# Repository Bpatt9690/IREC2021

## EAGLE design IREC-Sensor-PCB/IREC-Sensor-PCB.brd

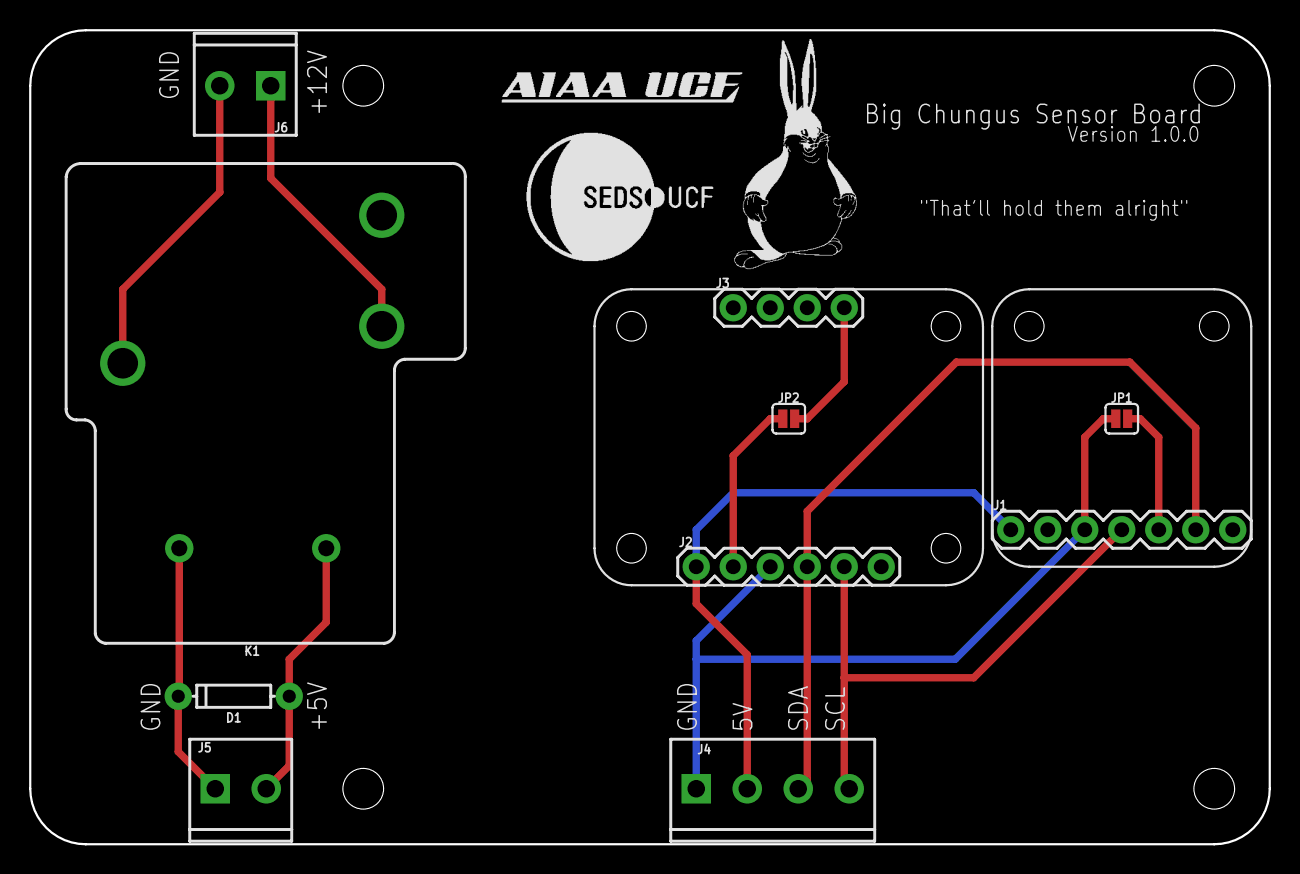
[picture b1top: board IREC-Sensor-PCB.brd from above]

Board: 2 copper layers, 85.1 x 55.9 mm, 11 parts (0 on the bottom side), 11 nets.

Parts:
D1: 200mA/100V/1V; DIODE-1N4148
FRAME1: FRAME-LETTER; CREATIVE_COMMONS
J1: 1X07
J2: 1X06
J3: 1X04
J4: SCREWTERMINAL-3.5MM-4
J5, J6: SCREWTERMINAL-3.5MM-2
JP1: HPT_ADDR; SMT-JUMPER_2_NO_SILK
JP2: AGM_ADDR; SMT-JUMPER_2_NO_SILK
K1: RELAY-SPDT-JQX-15F; RELAY-T90

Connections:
3V_AGM: J2.2, JP2.1
5V: J1.1, J2.1, J4.2
AD_AGM: J3.4, JP2.2
AD_HPT: J1.5, JP1.2
GND: J1.3, J2.3, J4.1, JP1.1
unnamed: D1.A, J5.2, K1.COIL2
unnamed: D1.C, J5.1, K1.COIL1
unnamed: J6.2, K1.MAIN
unnamed: J6.1, K1.NO
SCL: J1.4, J2.5, J4.4
SDA: J1.6, J2.4, J4.3

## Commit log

2020-08-04 Setting Up Repo
2020-08-04 Added backup for Launch_Pad_Files
2020-08-18 Fixed bug in cfTest.py
2020-08-27 Restructuring repo
2020-08-28 Added Sensor PCB files
2020-08-29 Updated Sensor PCB files
2020-08-30 Updated Logo Folder
2020-08-30 Set up board dimensions
2020-08-31 Completed layout
    Completed board layout
2020-08-31 Final 1.0.0 Board!
    Board is complete!
    - Adjusted board dimensions
    - Added relay
    - Added I2C address switches
2020-09-03 Restructuring for anticipated cold flow test
2020-09-03 Restructuring for anticipated Cold Flow presentation
2020-09-03 Fixed Directory Names and Structure
2020-10-01 Implemented ignition capabilities into the system
2020-10-01 Created Directory for Flight Computer Dev
2020-10-02 Added flight code to test sensors
2020-10-03 Restructured Directories; Included serial thread for load cell data
2020-10-10 Mapped GPIO per diagram
2020-10-10 Threading works need to work on joining
2020-10-10 Adjusted timer for actuators; Added threading
2020-10-14 Added to Avionics Src Code
2020-10-14 Added LoRa Reciever code
2020-10-19 Added Backup data files and error logging
2020-10-19 Added loadcell Arduino code
2020-10-21 Pictures
2020-11-02 Added defense against improper key input
2020-11-03 Update coldflow.py
    Changed countdown from 10->5 seconds
2020-11-03 Update GSEActuator.py
    Added dual ignition sequence.
2020-11-06 Propulsion Data Acquistion Code
2020-11-07 added serial2csv to repo
2020-11-08 Added serialToCSV for Data Aqcuisition
2020-11-10 Added Keyboard Interrupt to GSEActuators.py
2020-11-10 Restructured directories, files renamed.
2020-11-10 Included alternate serial2csv
2020-11-13 Updated Ignition Sequence
2020-11-13 Added comments for debugging ignition
2020-11-13 Updated GSE Control Station to reflect elapsed ignition time
2020-11-13 Propulsion DAQ Folder Name and commented out unecessarily line in Serial2CSV
2020-11-14 Changed Control Station to send ignition sequence start at t-0
2020-11-24 Updates for last static fire

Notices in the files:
parts and their libraries:
SparkFun-Aesthetics: Licensing: Creative Commons ShareAlike 4.0 International - https://creativecommons.org/licenses/by-sa/4.0
SparkFun-Aesthetics: Released under the Creative Commons Attribution Share-Alike 4.0 License
SparkFun-Aesthetics: https://creativecommons.org/licenses/by-sa/4.0
